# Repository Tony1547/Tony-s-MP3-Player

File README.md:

# Tony-s-MP3-Player
A custom MP3 player designed to bypass my school's ban on all cellular devices, which also bans over half the internet. How am I supposed to listen to my TF2 soundtrack? This project is also a good first step before I have to make my robot arm's PCB.

Onshape Link: https://cad.onshape.com/documents/4ae9d4a6ef44a3dbc4a2c6f3/w/3289807ef25710fc241d0646/e/3b21fd57c49c14028b7a0996?renderMode=0&uiState=694b6cd45adb009592eded3d 

Google Sheets if needed: https://docs.google.com/spreadsheets/d/1tBs17rBeQA4046zbtyh8lai0--RzHnu4pUclCCczuA0/edit?gid=1155955550#gid=1155955550

This is my first non-tutorial followed PCB! The following are pictures of the MP3 in Onshape and Kicad

|  1 | C2962032  | HYCW19-TF09-205B                                        | HOAUC                     | SMD                            |   | Micro SD card (TF card) Connector and Ejector Push-Push Surface Mount                       | yes |   5 |   5 |   5 |  0.3308 |  1.65 |   1.65 |
|---:|-----------|---------------------------------------------------------|---------------------------|--------------------------------|---|---------------------------------------------------------------------------------------------|-----|----:|----:|----:|--------:|------:|-------:|
|  2 | C105578   | RC0603FR-071ML                                          | YAGEO                     |                            603 |   | 100mW 1MΩ 75V ±100ppm/℃ Thick Film Resistor ±1% 0603 Chip Resistor - Surface Mount RoHS     | yes | 100 | 100 | 100 |  0.0012 |  0.12 |   1.77 |
|  3 | C14675    | RC0603FR-07100KL                                        | YAGEO                     |                            603 |   | 100mW 100kΩ 75V ±100ppm/℃ Thick Film Resistor ±1% 0603 Chip Resistor - Surface Mount RoHS   | yes | 100 | 100 | 100 |   0.001 |   0.1 |   1.87 |
|  4 | C22843    | 0603WAF1501T5E                                          | UNI-ROYAL                 |                            603 |   | 1.5kΩ ±1% 100mW 0603 Thick Film Resistor                                                    | yes | 100 | 100 | 100 |  0.0011 |  0.11 |   1.98 |
|  5 | C870490   | RT1206BRD071K13L                                        | YAGEO                     |                           1206 |   | 250mW 1.13kΩ 200V ±25ppm/℃ Thin Film Resistor ±0.1% 1206 Chip Resistor - Surface Mount RoHS | yes |  10 |  10 |  10 |  0.0693 |  0.69 |   2.67 |
|  6 | C2906979  | FRC0603F1801TS                                          | FOJAN                     |                            603 |   | 1.8kΩ ±1% 100mW 0603 Thick Film Resistor                                                    | yes | 100 | 100 | 100 |   0.001 |   0.1 |   2.77 |
|  7 | C2907044  | FRC0603F5101TS                                          | FOJAN                     |                            603 |   | 5.1kΩ ±1% 100mW 0603 Thick Film Resistor                                                    | yes | 100 | 100 | 100 |  0.0009 |  0.09 |   2.86 |
|  8 | C782233   | RN73H1JTTD4642B25                                       | KOA                       |                            603 |   | 100mW 46.4kΩ ±25ppm/℃ Metal Film Resistor ±0.1% 0603 Chip Resistor - Surface Mount RoHS     | yes |   1 |   1 |   1 |  0.2313 |  0.23 |   3.09 |
|  9 | C1705     | CL10A475KP8NNNC                                         | Samsung Electro-Mechanics |                            603 |   | 4.7uF ±10% 10V Ceramic Capacitor X5R 0603                                                   | yes |  50 |  50 |  50 |  0.0051 |  0.26 |   3.35 |
| 10 | C1653     | CL10C220JB8NNNC                                         | Samsung Electro-Mechanics |                            603 |   | 22pF ±5% 50V Ceramic Capacitor C0G 0603                                                     | yes | 100 | 100 | 100 |  0.0038 |  0.38 |   3.73 |
| 11 | C96346    | RC0805FR-07100KL                                        | YAGEO                     |                            805 |   | 125mW 100kΩ 150V ±100ppm/℃ Thick Film Resistor ±1% 0805 Chip Resistor - Surface Mount RoHS  | yes | 100 | 100 | 100 |  0.0022 |  0.22 |   3.95 |
| 12 | C28323    | CL21B105KBFNNNE                                         | Samsung Electro-Mechanics |                            805 |   | 1uF ±10% 50V Ceramic Capacitor X7R 0805                                                     | yes |  20 |  20 |  20 |  0.0092 |  0.18 |   4.13 |
| 13 | C5189822  | CS2012X7R106M100NRE                                     | SAMWHA                    |                            805 |   | 10uF ±20% 10V Ceramic Capacitor X7R 0805                                                    | yes |  50 |  50 |  50 |  0.0074 |  0.37 |    4.5 |
| 14 | C170101   | CL31B225KCHSNNE                                         | Samsung Electro-Mechanics |                           1206 |   | 2.2uF ±10% 100V Ceramic Capacitor X7R 1206                                                  | yes |   5 |   5 |   5 |  0.0758 |  0.38 |   4.88 |
| 15 | C22548    | RC0603FR-071KL                                          | YAGEO                     |                            603 |   | 100mW 1kΩ 75V ±100ppm/℃ Thick Film Resistor ±1% 0603 Chip Resistor - Surface Mount RoHS     | yes | 100 | 100 | 100 |  0.0011 |  0.11 |   4.99 |
| 16 | C15850    | CL21A106KAYNNNE                                         | Samsung Electro-Mechanics |                            805 |   | 10uF ±10% 25V Ceramic Capacitor X5R 0805                                                    | yes |  20 |  20 |  20 |  0.0102 |   0.2 |   5.19 |
| 17 | C98220    | RC0603FR-0710KL                                         | YAGEO                     |                            603 |   | 100mW 10kΩ 75V ±100ppm/℃ Thick Film Resistor ±1% 0603 Chip Resistor - Surface Mount RoHS    | yes | 100 | 100 | 100 |  0.0011 |  0.11 |    5.3 |
| 18 | C1591     | CL10B104KB8NNNC                                         | Samsung Electro-Mechanics |                            603 |   | 100nF ±10% 50V Ceramic Capacitor X7R 0603                                                   | yes | 100 | 100 | 100 |  0.0026 |  0.26 |   5.56 |
| 19 | C19171390 | YLED0603R                                               | YONGYUTAI                 |                            603 |   | Red LED Indication - Discrete 1.8V~2.4V 0603                                                | yes | 100 | 100 | 100 |  0.0055 |  0.55 |   6.11 |
| 20 | C157929   | S3B-PH-K-S(LF)(SN)                                      | JST                       | Through Hole,Right Angle,P=2mm |   | Connector Header 3 position 2mm Pitch 2A Right Angle -25℃~+85℃                              | yes |  10 |  10 |  10 |  0.0433 |  0.43 |   6.54 |
| 21 | C2765186  | TYPE-C 16PIN 2MD(073)                                   | SHOU HAN                  | SMD                            |   | USB-C (USB TYPE-C) Receptacle Connector 16 Position Surface Mount, Right Angle              | yes |  20 |  20 |  20 |    0.06 |   1.2 |   7.74 |
| 22 | C4991872  | SJ-3523-SMT-TR                                          | CUI                       | SMD                            |   | 1A 12V                                                                                      | yes |   1 |   1 |   1 |  1.3366 |  1.34 |   9.08 |
| 23 | C19171394 | YLED0603B                                               | YONGYUTAI                 |                            603 |   | Blue LED Indication - Discrete 2.6V~3.2V 0603                                               | yes | 100 | 100 | 100 |   0.004 |   0.4 |   9.48 |
| 24 | C1338432  | STM32F401VEH6                                           | ST                        | UFBGA-100                      |   | ARM Cortex-M4 84MHz 81 UFBGA-100 Microcontrollers RoHS                                      | yes |   1 |   1 |   1 |  7.9079 |  7.91 |  17.39 |
| 25 | C5248081  | HS91L02W2C01                                            | HS                        | -                              |   | 0.91 128x32 SSD1306 I2C LCD, OLED, Graphic RoHS                                             | yes |   1 |   1 |   1 |  1.9851 |  1.99 |  19.38 |
| 26 | C69901    | TPA6132A2RTER                                           | TI                        | WQFN-16-EP(3x3)                |   | 2-Channel Class AB WQFN-16-EP(3x3) Audio Amplifiers RoHS                                    | yes |   1 |   1 |   1 |  1.2295 |  1.23 |  20.61 |
| 27 | C486306   | VS1063A-L                                               | VLSI                      | LQFP-48(7x7)                   |   | 48kHz LQFP-48(7x7) Audio Special Purpose RoHS                                               | yes |   1 |   1 |   1 |  9.3147 |  9.31 |  29.92 |
| 28 | C15464    | BQ24075RGTR                                             | TI                        | QFN-16-EP(3x3)                 |   | 4.35V~6.4V Lithium Battery 1.5A QFN-16-EP(3x3) Battery Chargers ICs RoHS                    | yes |   1 |   1 |   1 |  0.8901 |  0.89 |  30.81 |
| 29 | C26537    | NCP1117ST33T3G                                          | onsemi                    | SOT-223                        |   | Linear Voltage Regulator IC Positive Fixed 1 Output 1A SOT-223                              | yes |   5 |   5 |   5 |  0.2344 |  1.17 |  31.98 |
| 30 | C720477   | TS-1088-AR02016                                         | XUNPU                     | SMD,4x3mm                      |   | Tactile Switch SPST 160gf 2mm SMD (SMT) Tab 4mm x 3mm Surface Mount                         | yes |  10 |  10 |  10 |  0.0423 |  0.42 |   32.4 |
| 31 | C7294738  | SD2012M28820001                                         | huaxindianzi              | HC-49S-SMD                     |   | Crystal 12.288MHz ±20ppm 20pF 80Ω HC-49S-SMD                                                | yes |   5 |   5 |   5 |   0.076 |  0.38 |  32.78 |
| 32 |           | 3.7V 500mAh Rechargeable Lithium Li-ion Polymer Battery |                           |                                |   | Battery                                                                                     |     |   1 |   1 |   1 |   $3.99 | $3.99 | $36.77 |
| 33 |           | PCB                                                     | JLCPCB                    |                                |   | Custom Printed Circuit Board                                                                |     |   1 |   1 |   1 |     0.4 |  5.12 | $41.89 |
| 34 |           | 3D Prints                                               |                           |                                |   | Case                                                                                        |     |   1 |   1 |   1 | Depends |       |        |

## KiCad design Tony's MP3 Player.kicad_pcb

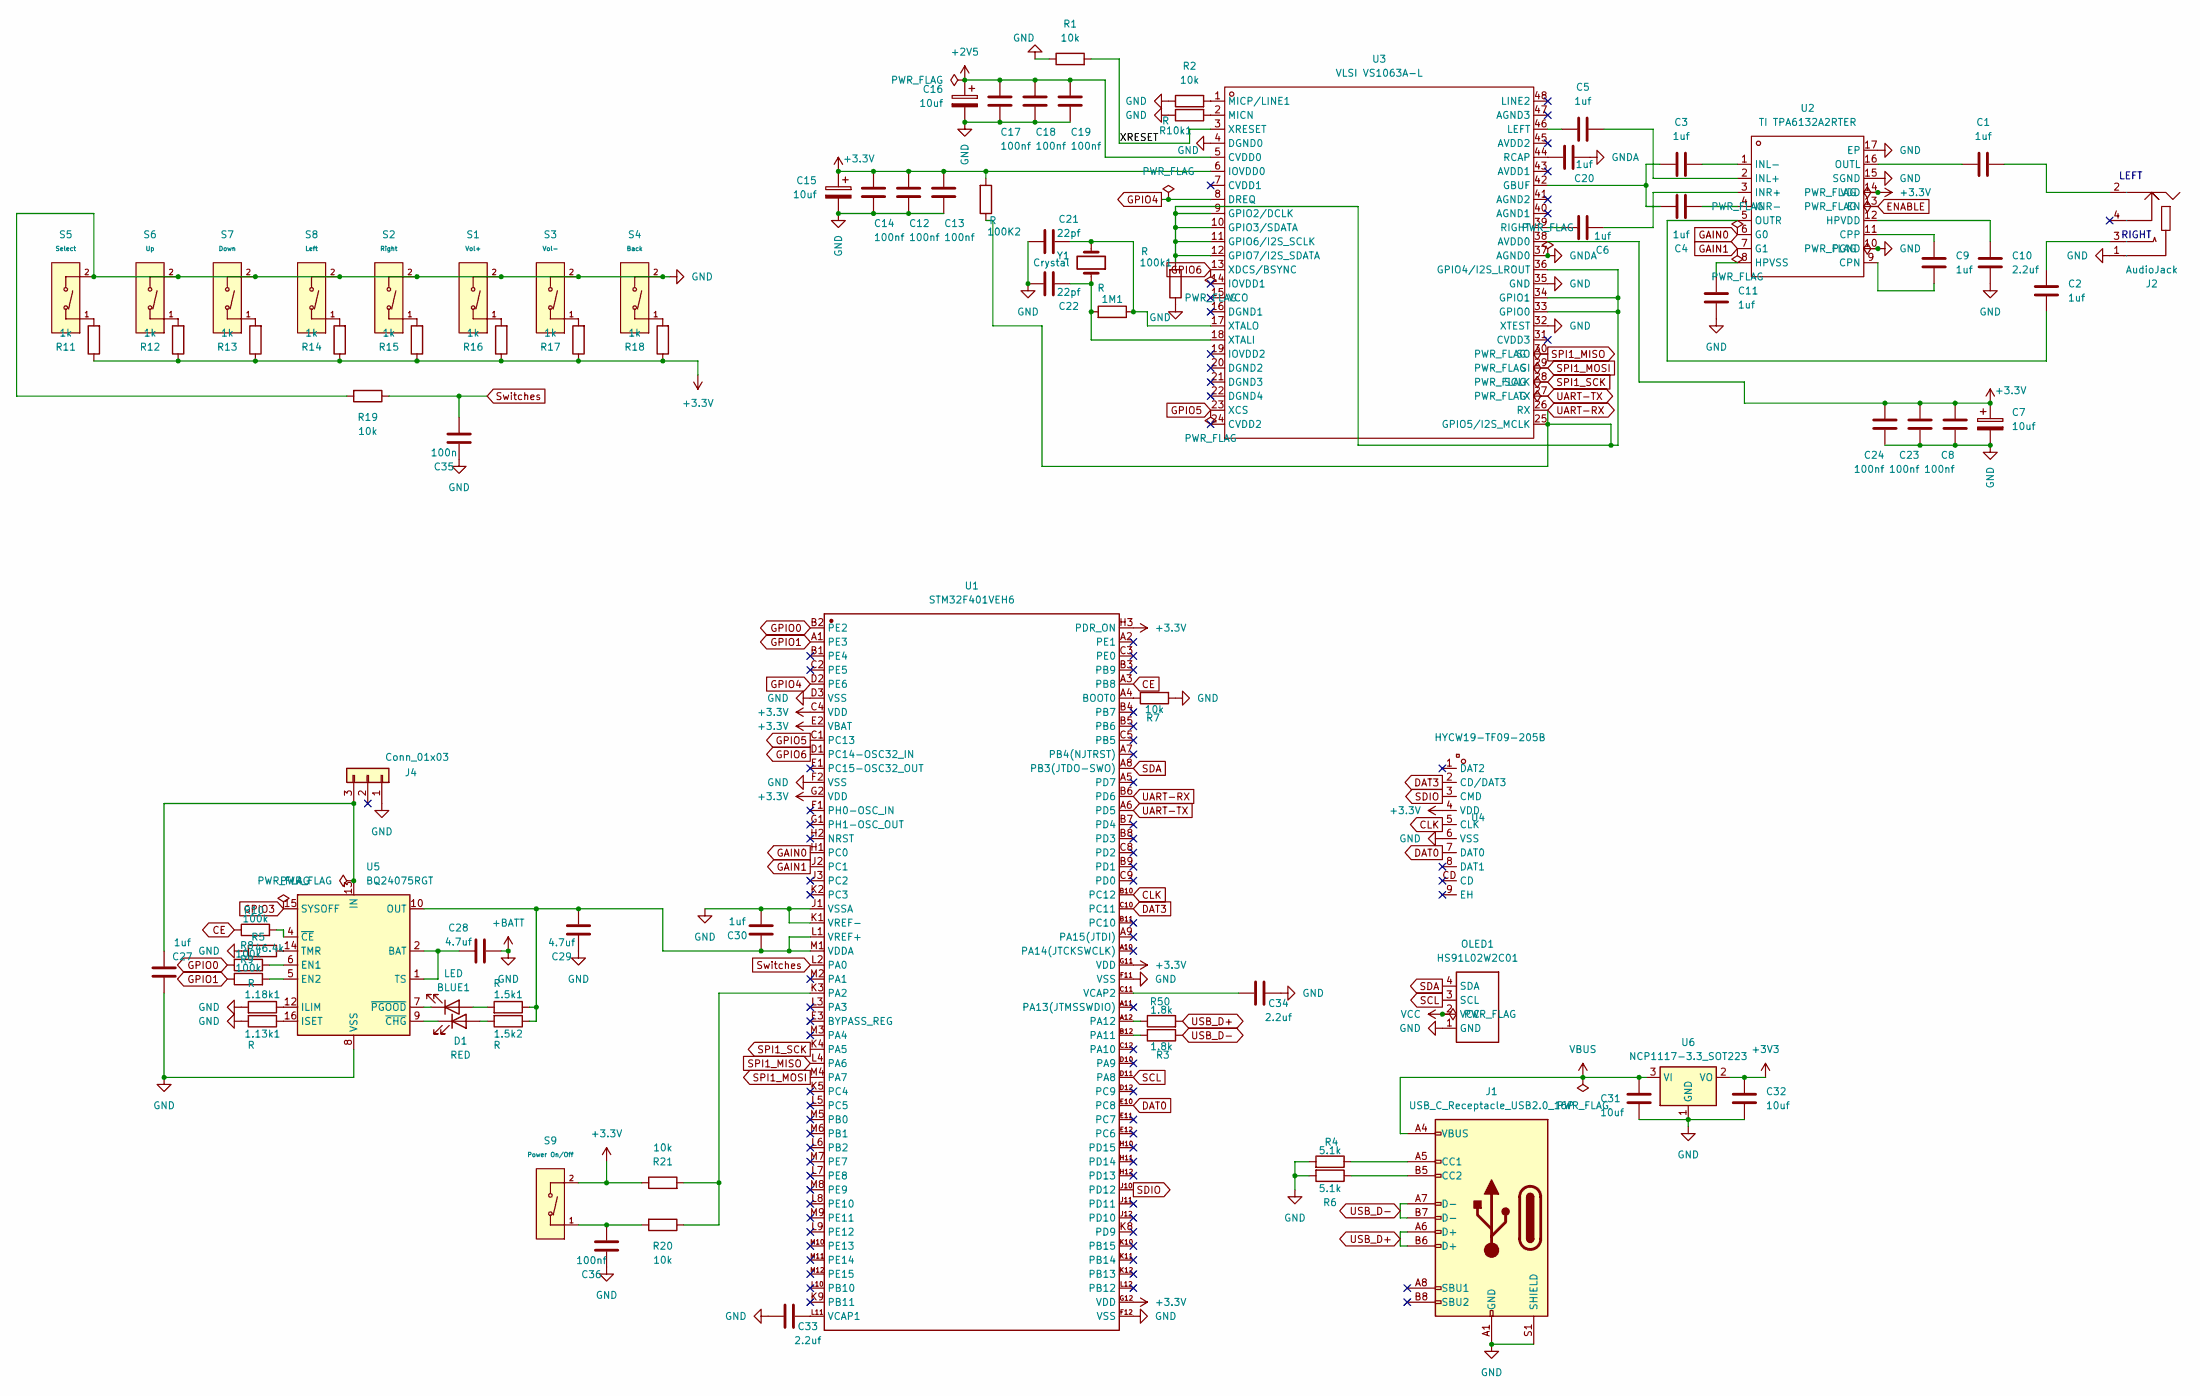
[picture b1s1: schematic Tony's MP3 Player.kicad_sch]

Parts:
1.5k1, 1.5k2, 1.13k1, 1.18k1, 1M1, 100K2, 100k1: R; R_0201_0603Metric_Pad0.64x0.40mm_HandSolder
BLUE1: LED; LED_0201_0603Metric_Pad0.64x0.40mm_HandSolder
C1, C2, C3, C4, C5, C6, C9, C11, C20, C27, C30: 1uf; C_0201_0603Metric_Pad0.64x0.40mm_HandSolder
C7, C15, C16: 10uf; CP_Axial_L10.0mm_D4.5mm_P15.00mm_Horizontal
C8, C12, C13, C14, C17, C18, C19, C23, C24, C36: 100nf; C_0201_0603Metric_Pad0.64x0.40mm_HandSolder
C10, C33, C34: 2.2uf; C_0201_0603Metric_Pad0.64x0.40mm_HandSolder
C21, C22: 22pf; C_0201_0603Metric_Pad0.64x0.40mm_HandSolder
C28, C29: 4.7uf; C_0201_0603Metric_Pad0.64x0.40mm_HandSolder
C31, C32: 10uf; C_0201_0603Metric_Pad0.64x0.40mm_HandSolder
C35: 100n; C_0201_0603Metric_Pad0.64x0.40mm_HandSolder
D1: RED; LED_0201_0603Metric_Pad0.64x0.40mm_HandSolder
J1: USB_C_Receptacle_USB2.0_16P; USB_C_Receptacle_Palconn_UTC16-G
J2: AudioJack; AUDIO-SMD_SJ-3524-SMT-TR-BE; Manufacturer Part SJ-3523-SMT-TR; LCSC Part Name SJ-3523-SMT-TR
J4: Conn_01x03; JST_PH_S3B-PH-K_1x03_P2.00mm_Horizontal
OLED1: HS91L02W2C01; OLED-TH_L38.0-W12.0_HS91L02W2C01; Manufacturer Part HS91L02W2C01
R1, R2, R7, R19, R20, R21: 10k; R_0201_0603Metric_Pad0.64x0.40mm_HandSolder
R3, R50: 1.8k; R_0201_0603Metric_Pad0.64x0.40mm_HandSolder
R4, R6: 5.1k; R_0201_0603Metric_Pad0.64x0.40mm_HandSolder
R5: 46.4k; R_0201_0603Metric_Pad0.64x0.40mm_HandSolder
R8, R9, R10: 100k; R_0201_0603Metric_Pad0.64x0.40mm_HandSolder
R10k1: R; R_0201_0603Metric_Pad0.64x0.40mm_HandSolder
R11, R12, R13, R14, R15, R16, R17, R18: 1k; R_0201_0603Metric_Pad0.64x0.40mm_HandSolder
S1: Vol+; SW_TS-1088-AR02016; Voltage Rating (Dc) 12V; Part TS-1088-AR02016; LCSC C720477
S2: Right; SW_TS-1088-AR02016; Voltage Rating (Dc) 12V; Part TS-1088-AR02016; LCSC C720477
S3: Vol-; SW_TS-1088-AR02016; Voltage Rating (Dc) 12V; Part TS-1088-AR02016; LCSC C720477
S4: Back; SW_TS-1088-AR02016; Voltage Rating (Dc) 12V; Part TS-1088-AR02016; LCSC C720477
S5: Select; SW_TS-1088-AR02016; Voltage Rating (Dc) 12V; Part TS-1088-AR02016; LCSC C720477
S6: Up; SW_TS-1088-AR02016; Voltage Rating (Dc) 12V; Part TS-1088-AR02016; LCSC C720477
S7: Down; SW_TS-1088-AR02016; Voltage Rating (Dc) 12V; Part TS-1088-AR02016; LCSC C720477
S8: Left; SW_TS-1088-AR02016; Voltage Rating (Dc) 12V; Part TS-1088-AR02016; LCSC C720477
S9: Power On/Off; SW_TS-1088-AR02016; Voltage Rating (Dc) 12V; Part TS-1088-AR02016; LCSC C720477
U1: STM32F401VEH6; UFBGA-100_L7.0-W7.0-P0.50-TL_ST_STM32; Manufacturer Part STM32F401VEH6
U2: TI TPA6132A2RTER; WQFN-16_L3.0-W3.0-P0.50-TL-EP1.6; Manufacturer Part TPA6132A2RTER; LCSC Part Name TPA6132A2RTER
U3: VLSI VS1063A-L; LQFP-48_L7.0-W7.0-P0.50-LS9.0-BL; Manufacturer Part VS1063A-L; LCSC Part Name VS1063A-L
U4: HYCW19-TF09-205B; MICRO-SD-SMD_HYCW19-TF09-205B; LCSC Part C2962032
U5: BQ24075RGT; VQFN-16-1EP_3x3mm_P0.5mm_EP1.6x1.6mm
U6: NCP1117-3.3_SOT223; SOT-223-3_TabPin2
Y1: Crystal; Crystal_SMD_MicroCrystal_CC1V-T1A-2Pin_8.0x3.7mm_HandSolder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

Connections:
+2V5: C16.1, C17.2, C18.2, C19.2, U3.5 (CVDD0)
+3.3V: 100K2.2, C7.1, C8.2, C12.2, C13.2, C14.2, C15.1, C23.2, C24.2, R11.1, R12.1, R13.1, R14.1, R15.1, R16.1, R17.1, R18.1, R21.1, S9.2 (B), U1.C4 (VDD), U1.E2 (VBAT), U1.G2 (VDD), U1.G11 (VDD), U1.G12 (VDD), U1.H3 (PDR_ON), U2.14 (VDD), U3.6 (IOVDD0), U3.38 (AVDD0), U4.4 (VDD)
+3V3: C32.1, U6.2 (VO)
+BATT: 1.13k1.2, 1.18k1.2, 100k1.1, C7.2, C8.1, C10.1, C11.1, C12.1, C13.1, C14.1, C15.2, C16.2, C17.1, C18.1, C19.1, C21.1, C22.1, C23.1, C24.1, C27.2, C28.2, C29.1, C30.1, C31.2, C32.2, C33.2, C34.1, C35.1, C36.1, J1.A1 (GND), J1.A12 (GND), J1.B1 (GND), J1.B12 (GND), J1.S1 (SHIELD), J2.1, J4.1, OLED1.1 (GND), R1.1, R2.1, R4.2, R5.2, R6.2, R7.2, R10k1.1, R19.2, S1.2 (B), S2.2 (B), S3.2 (B), S4.2 (B), S5.2 (B), S6.2 (B), S7.2 (B), S8.2 (B), U1.D3 (VSS), U1.F2 (VSS), U1.F11 (VSS), U1.F12 (VSS), U1.J1 (VSSA), U1.K1 (VREF-), U2.10 (PGND), U2.15 (SGND), U2.17 (EP), U3.4 (DGND0), U3.32 (XTEST), U3.35 (GND), U4.6 (VSS), U5.8 (VSS), U5.17 (VSS), U6.1 (GND)
/XRESET: R1.2, U3.3 (XRESET)
CE: R10.1, U1.A3 (PB8)
CLK: U1.B10 (PC12), U4.5 (CLK)
DAT0: U1.E10 (PC8), U4.7 (DAT0)
DAT3: U1.C10 (PC11), U4.2 (CD/DAT3)
ENABLE: U2.13 (EN)
GAIN0: U1.H1 (PC0), U2.6 (G0)
GAIN1: U1.J2 (PC1), U2.7 (G1)
GNDA: C20.1, U3.37 (AGND0)
GPIO0: R8.1, U1.B2 (PE2)
GPIO1: R9.1, U1.A1 (PE3)
GPIO3: U5.15 (SYSOFF)
GPIO4: U1.D2 (PE6), U3.8 (DREQ)
GPIO5: U1.C1 (PC13), U3.23 (XCS)
GPIO6: U1.D1 (PC14-OSC32_IN), U3.13 (XDCS/BSYNC)
unnamed: 1.5k1.2, BLUE1.2 (A)
unnamed: BLUE1.1 (K), U5.7 (~PGOOD)
unnamed: C1.2, J2.2
unnamed: C2.2, J2.3
unnamed: 1.5k2.2, D1.2 (A)
unnamed: D1.1 (K), U5.9 (~CHG)
unnamed: J1.A5 (CC1), R4.1
unnamed: J1.B5 (CC2), R6.1
unnamed: C27.1, J4.3, U5.13 (IN)
unnamed: R16.2, S1.1 (A)
unnamed: R15.2, S2.1 (A)
unnamed: R17.2, S3.1 (A)
unnamed: R18.2, S4.1 (A)
unnamed: R11.2, S5.1 (A)
unnamed: R12.2, S6.1 (A)
unnamed: R13.2, S7.1 (A)
unnamed: R14.2, S8.1 (A)
unnamed: C36.2, R20.2, S9.1 (A)
unnamed: R7.1, U1.A4 (BOOT0)
unnamed: R20.1, R21.2, U1.K3 (PA2)
unnamed: R3.2, U1.B12 (PA11)
unnamed: R50.1, U1.A12
unnamed: C33.1, U1.L11 (VCAP1)
unnamed: C34.2, U1.C11 (VCAP2)
unnamed: 1.5k1.1, 1.5k2.1, C29.2, C30.2, U1.L1 (VREF+), U1.M1 (VDDA), U5.10 (OUT), U5.11 (OUT)
unnamed: C9.1, U2.9 (CPN)
unnamed: C9.2, U2.11 (CPP)
unnamed: C10.2, U2.12 (HPVDD)
unnamed: C11.2, U2.8 (HPVSS)
unnamed: C5.2, U2.2 (INL+)
unnamed: C3.2, U2.1 (INL-)
unnamed: C6.2, U2.3 (INR+)
unnamed: C4.2, U2.4 (INR-)
unnamed: C1.1, U2.16 (OUTL)
unnamed: C2.1, U2.5 (OUTR)
unnamed: C3.1, C4.1, U3.42 (GBUF)
unnamed: C5.1, U3.46 (LEFT)
unnamed: R10k1.2, U3.2 (MICN)
unnamed: R2.2, U3.1 (MICP/LINE1)
unnamed: C20.2, U3.44 (RCAP)
unnamed: C6.1, U3.39 (RIGHT)
unnamed: 1M1.2, C22.2, U3.18 (XTALI), Y1.1
unnamed: 1M1.1, C21.2, U3.17 (XTALO), Y1.2
unnamed: R8.2, U5.6 (EN1)
unnamed: R9.2, U5.5 (EN2)
unnamed: 1.18k1.1, U5.12 (ILIM)
unnamed: 1.13k1.1, U5.16 (ISET)
unnamed: R5.1, U5.14 (TMR)
unnamed: C28.1, U5.1 (TS), U5.2 (BAT), U5.3 (BAT)
unnamed: R10.2, U5.4 (~CE)
SCL: OLED1.3 (SCL), U1.D11 (PA8)
SDA: OLED1.4 (SDA), U1.A8 (PB3(JTDO-SWO))
SDIO: U1.J10 (PD12), U4.3 (CMD)
SPI1_MISO: U1.L4 (PA6), U3.30 (SO)
SPI1_MOSI: U1.M4 (PA7), U3.29 (SI)
SPI1_SCK: U1.K4 (PA5), U3.28 (SCLK)
Switches: C35.2, R19.1, U1.L2 (PA0)
UART-RX: 100K2.1, 100k1.2, U1.B6 (PD6), U3.9 (GPIO2/DCLK), U3.10 (GPIO3/SDATA), U3.11 (GPIO6/I2S_SCLK), U3.12 (GPIO7/I2S_SDATA), U3.25 (GPIO5/I2S_MCLK), U3.26 (RX), U3.33 (GPIO0), U3.34 (GPIO1), U3.36 (GPIO4/I2S_LROUT)
UART-TX: U1.A6 (PD5), U3.27 (TX)
USB_D+: J1.A6 (D+), J1.B6 (D+), R50.2
USB_D-: J1.A7 (D-), J1.B7 (D-), R3.1
VBUS: C31.1, J1.A4 (VBUS), J1.A9 (VBUS), J1.B4 (VBUS), J1.B9 (VBUS), U6.3 (VI)
VCC: OLED1.2 (VCC)

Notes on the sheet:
RIGHT
LEFT

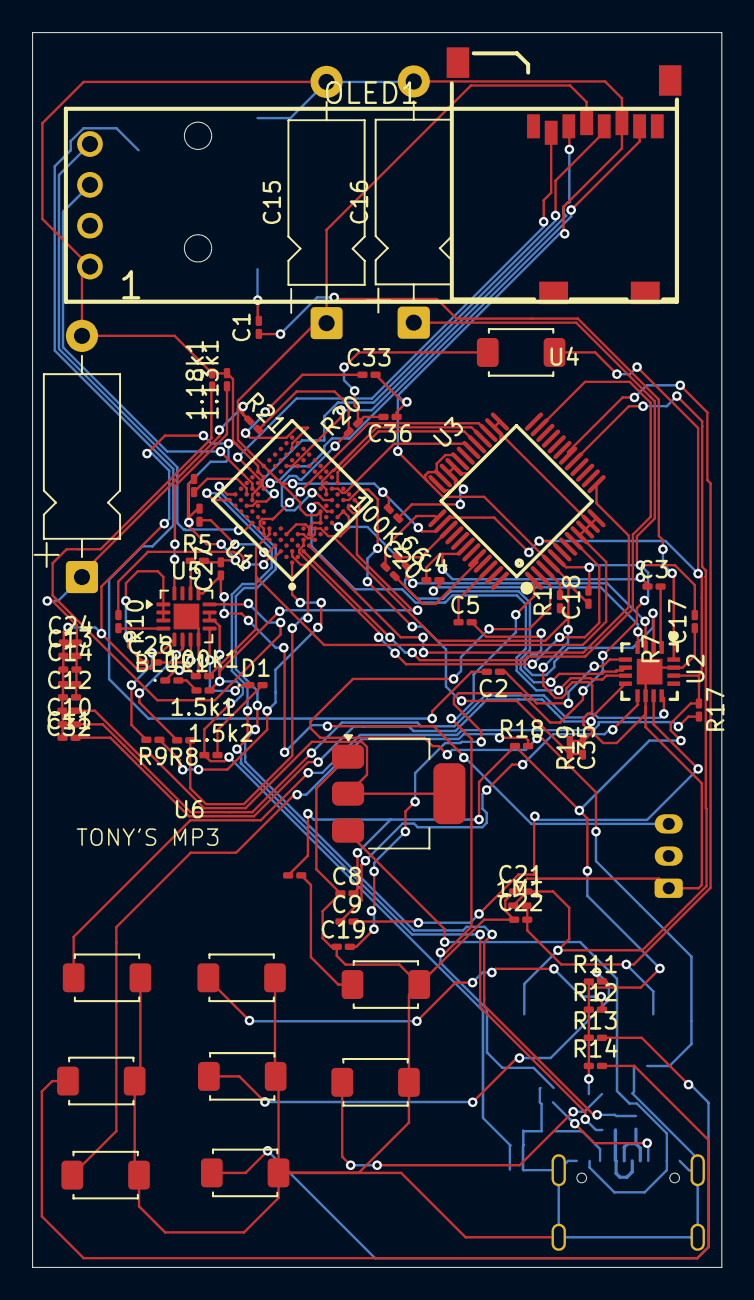
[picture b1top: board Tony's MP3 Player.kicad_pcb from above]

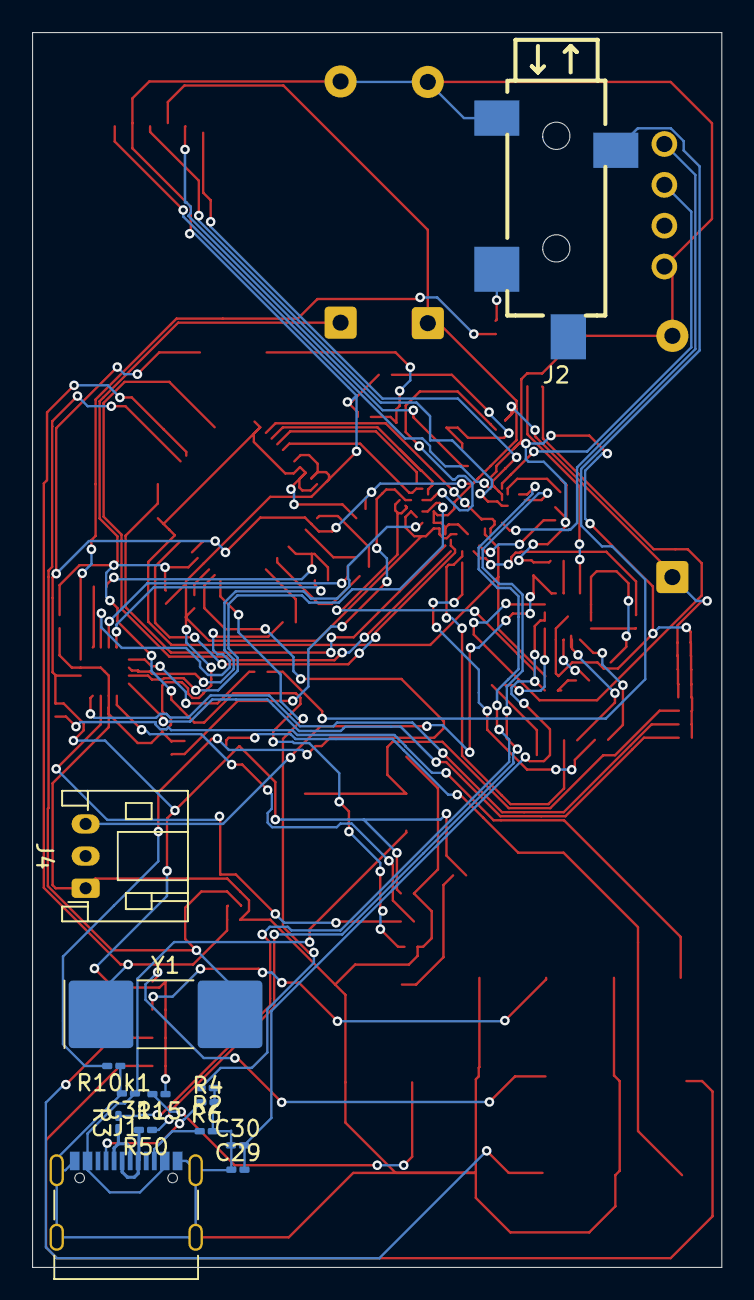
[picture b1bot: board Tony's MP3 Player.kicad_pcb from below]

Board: 2 copper layers, 42.9 x 76.8 mm, 86 parts (14 on the bottom side), 79 nets.

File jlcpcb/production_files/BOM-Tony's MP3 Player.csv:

Comment,Designator,Footprint,LCSC,Quantity
Back,S4,SW_TS-1088-AR02016,C720477,1
Down,S7,SW_TS-1088-AR02016,C720477,1
HYCW19-TF09-205B,U4,MICRO-SD-SMD_HYCW19-TF09-205B,C2962032,1
Left,S8,SW_TS-1088-AR02016,C720477,1
Power On/Off,S9,SW_TS-1088-AR02016,C720477,1
Right,S2,SW_TS-1088-AR02016,C720477,1
Select,S5,SW_TS-1088-AR02016,C720477,1
Up,S6,SW_TS-1088-AR02016,C720477,1
Vol+,S1,SW_TS-1088-AR02016,C720477,1
Vol-,S3,SW_TS-1088-AR02016,C720477,1
10uf,C31,C_0201_0603Metric_Pad0.64x0.40mm_HandSolder,,1
R,R10k1,R_0201_0603Metric_Pad0.64x0.40mm_HandSolder,,1
4.7uf,C29,C_0201_0603Metric_Pad0.64x0.40mm_HandSolder,,1
2.2uf,C33,C_0201_0603Metric_Pad0.64x0.40mm_HandSolder,,1
1uf,C30,C_0201_0603Metric_Pad0.64x0.40mm_HandSolder,,1
5.1k,R4,R_0201_0603Metric_Pad0.64x0.40mm_HandSolder,,1
1k,R15,R_0201_0603Metric_Pad0.64x0.40mm_HandSolder,,1
10k,R2,R_0201_0603Metric_Pad0.64x0.40mm_HandSolder,,1
5.1k,R6,R_0201_0603Metric_Pad0.64x0.40mm_HandSolder,,1
1.8k,R3,R_0201_0603Metric_Pad0.64x0.40mm_HandSolder,,1
10k,R21,R_0201_0603Metric_Pad0.64x0.40mm_HandSolder,,1
1uf,C20,C_0201_0603Metric_Pad0.64x0.40mm_HandSolder,,1
Crystal,Y1,Crystal_SMD_MicroCrystal_CC1V-T1A-2Pin_8.0x3.7mm_HandSoldering,,1
NCP1117-3.3_SOT223,U6,SOT-223-3_TabPin2,,1
BQ24075RGT,U5,VQFN-16-1EP_3x3mm_P0.5mm_EP1.6x1.6mm,,1
VLSI VS1063A-L,U3,LQFP-48_L7.0-W7.0-P0.50-LS9.0-BL,,1
TI TPA6132A2RTER,U2,WQFN-16_L3.0-W3.0-P0.50-TL-EP1.6,,1
STM32F401VEH6,U1,UFBGA-100_L7.0-W7.0-P0.50-TL_ST_STM32,,1
1.8k,R50,R_0201_0603Metric_Pad0.64x0.40mm_HandSolder,,1
10k,R20,R_0201_0603Metric_Pad0.64x0.40mm_HandSolder,,1
10k,R19,R_0201_0603Metric_Pad0.64x0.40mm_HandSolder,,1
1k,R18,R_0201_0603Metric_Pad0.64x0.40mm_HandSolder,,1
1k,R17,R_0201_0603Metric_Pad0.64x0.40mm_HandSolder,,1
1k,R16,R_0201_0603Metric_Pad0.64x0.40mm_HandSolder,,1
1k,R14,R_0201_0603Metric_Pad0.64x0.40mm_HandSolder,,1
1k,R13,R_0201_0603Metric_Pad0.64x0.40mm_HandSolder,,1
1k,R12,R_0201_0603Metric_Pad0.64x0.40mm_HandSolder,,1
1k,R11,R_0201_0603Metric_Pad0.64x0.40mm_HandSolder,,1
100k,R10,R_0201_0603Metric_Pad0.64x0.40mm_HandSolder,,1
100k,R9,R_0201_0603Metric_Pad0.64x0.40mm_HandSolder,,1
100k,R8,R_0201_0603Metric_Pad0.64x0.40mm_HandSolder,,1
10k,R7,R_0201_0603Metric_Pad0.64x0.40mm_HandSolder,,1
46.4k,R5,R_0201_0603Metric_Pad0.64x0.40mm_HandSolder,,1
10k,R1,R_0201_0603Metric_Pad0.64x0.40mm_HandSolder,,1
HS91L02W2C01,OLED1,OLED-TH_L38.0-W12.0_HS91L02W2C01,,1
Conn_01x03,J4,JST_PH_S3B-PH-K_1x03_P2.00mm_Horizontal,,1
AudioJack,J2,AUDIO-SMD_SJ-3524-SMT-TR-BE,,1
USB_C_Receptacle_USB2.0_16P,J1,USB_C_Receptacle_Palconn_UTC16-G,,1
RED,D1,LED_0201_0603Metric_Pad0.64x0.40mm_HandSolder,,1
100nf,C36,C_0201_0603Metric_Pad0.64x0.40mm_HandSolder,,1
100n,C35,C_0201_0603Metric_Pad0.64x0.40mm_HandSolder,,1
2.2uf,C34,C_0201_0603Metric_Pad0.64x0.40mm_HandSolder,,1
10uf,C32,C_0201_0603Metric_Pad0.64x0.40mm_HandSolder,,1
4.7uf,C28,C_0201_0603Metric_Pad0.64x0.40mm_HandSolder,,1
1uf,C27,C_0201_0603Metric_Pad0.64x0.40mm_HandSolder,,1
100nf,C23,C_0201_0603Metric_Pad0.64x0.40mm_HandSolder,,1
22pf,C22,C_0201_0603Metric_Pad0.64x0.40mm_HandSolder,,1
22pf,C21,C_0201_0603Metric_Pad0.64x0.40mm_HandSolder,,1
100nf,C19,C_0201_0603Metric_Pad0.64x0.40mm_HandSolder,,1
100nf,C18,C_0201_0603Metric_Pad0.64x0.40mm_HandSolder,,1
100nf,C17,C_0201_0603Metric_Pad0.64x0.40mm_HandSolder,,1
10uf,C16,CP_Axial_L10.0mm_D4.5mm_P15.00mm_Horizontal,,1
10uf,C15,CP_Axial_L10.0mm_D4.5mm_P15.00mm_Horizontal,,1
100nf,C14,C_0201_0603Metric_Pad0.64x0.40mm_HandSolder,,1
100nf,C13,C_0201_0603Metric_Pad0.64x0.40mm_HandSolder,,1
100nf,C12,C_0201_0603Metric_Pad0.64x0.40mm_HandSolder,,1
1uf,C11,C_0201_0603Metric_Pad0.64x0.40mm_HandSolder,,1
2.2uf,C10,C_0201_0603Metric_Pad0.64x0.40mm_HandSolder,,1
1uf,C9,C_0201_0603Metric_Pad0.64x0.40mm_HandSolder,,1
100nf,C8,C_0201_0603Metric_Pad0.64x0.40mm_HandSolder,,1
10uf,C7,CP_Axial_L10.0mm_D4.5mm_P15.00mm_Horizontal,,1
1uf,C6,C_0201_0603Metric_Pad0.64x0.40mm_HandSolder,,1
1uf,C5,C_0201_0603Metric_Pad0.64x0.40mm_HandSolder,,1
1uf,C4,C_0201_0603Metric_Pad0.64x0.40mm_HandSolder,,1
1uf,C3,C_0201_0603Metric_Pad0.64x0.40mm_HandSolder,,1
1uf,C2,C_0201_0603Metric_Pad0.64x0.40mm_HandSolder,,1
1uf,C1,C_0201_0603Metric_Pad0.64x0.40mm_HandSolder,,1
LED,BLUE1,LED_0201_0603Metric_Pad0.64x0.40mm_HandSolder,,1
R,100K2,R_0201_0603Metric_Pad0.64x0.40mm_HandSolder,,1
R,100k1,R_0201_0603Metric_Pad0.64x0.40mm_HandSolder,,1
R,1M1,R_0201_0603Metric_Pad0.64x0.40mm_HandSolder,,1
R,1.18k1,R_0201_0603Metric_Pad0.64x0.40mm_HandSolder,,1
R,1.13k1,R_0201_0603Metric_Pad0.64x0.40mm_HandSolder,,1
R,1.5k2,R_0201_0603Metric_Pad0.64x0.40mm_HandSolder,,1
R,1.5k1,R_0201_0603Metric_Pad0.64x0.40mm_HandSolder,,1

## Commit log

2025-12-26 copy files
2025-12-26 move gerb files
2026-01-01 organize
